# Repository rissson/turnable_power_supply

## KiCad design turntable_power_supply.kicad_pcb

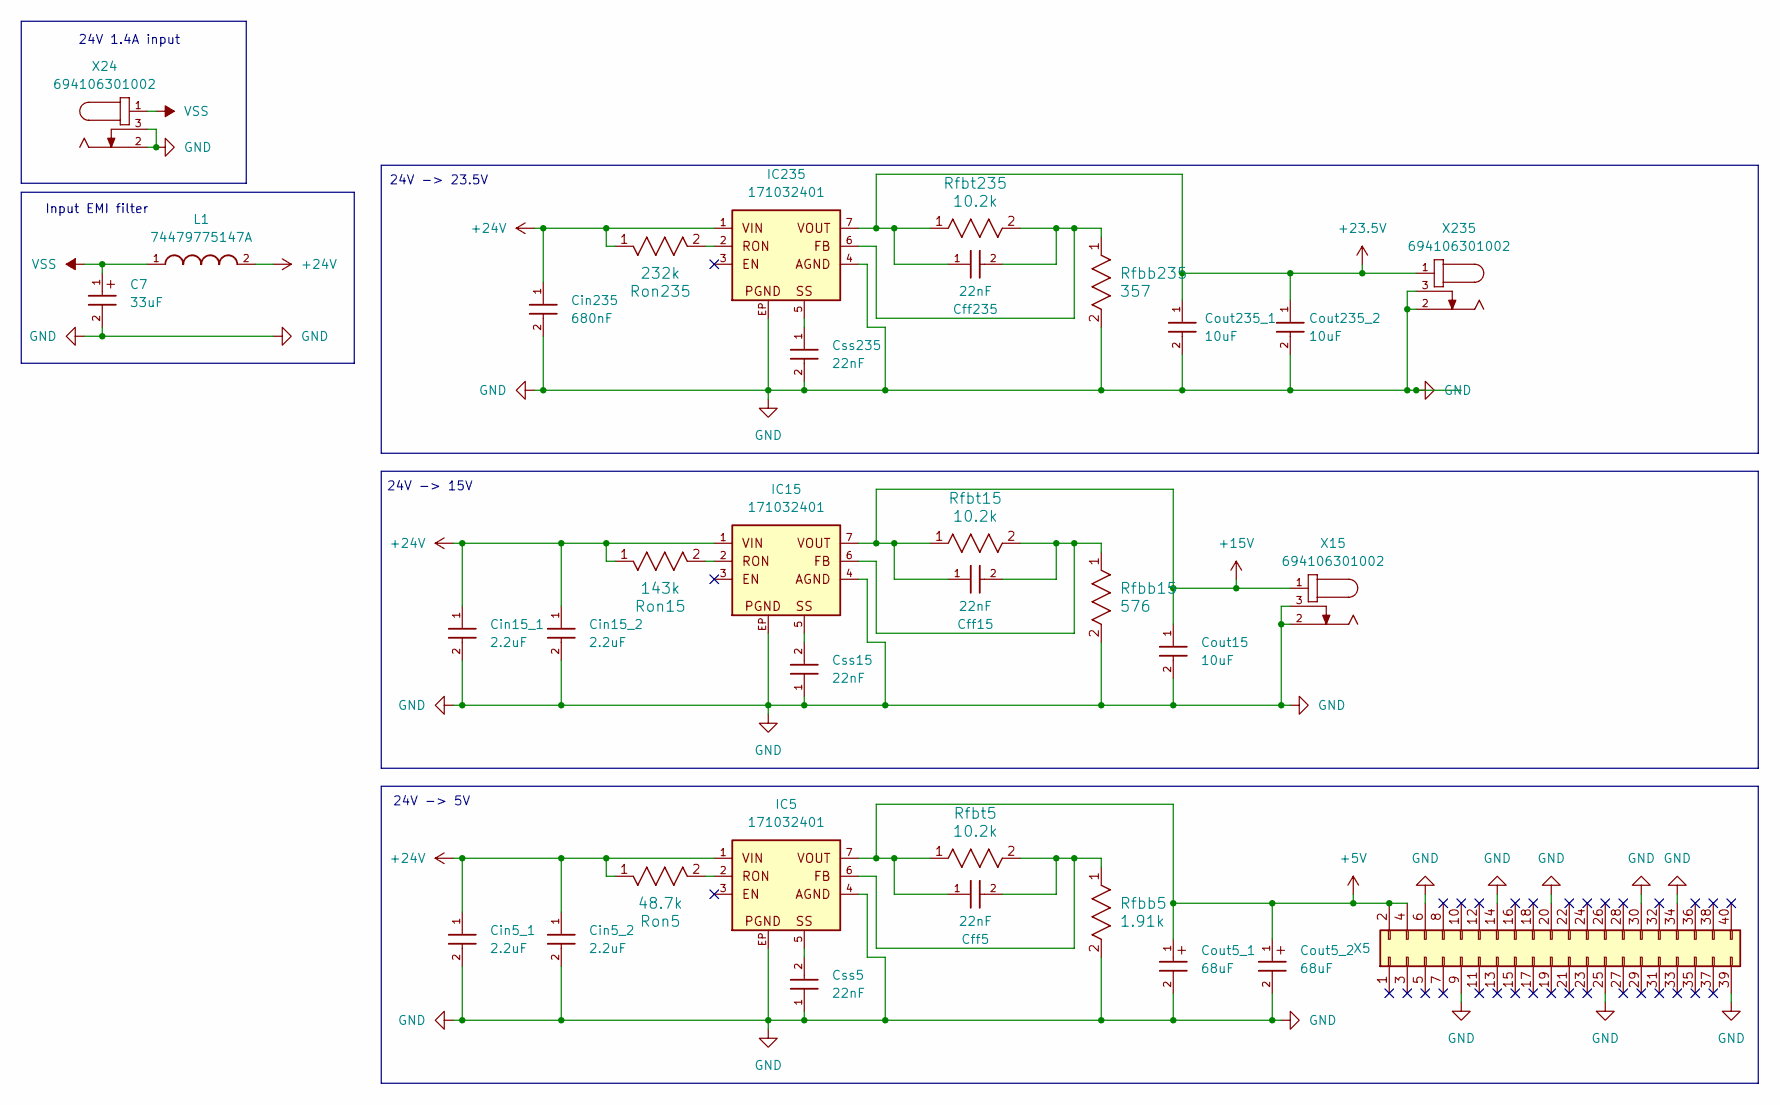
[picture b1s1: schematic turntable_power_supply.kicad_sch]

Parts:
C7: 33uF; 875115655013
Cff5, Cff15, Cff235: 22nF; 885012008009
Cin5_1, Cin5_2, Cin15_1, Cin15_2: 2.2uF; 885012210032
Cin235: 680nF; 885012210030
Cout5_1, Cout5_2: 68uF; 870235674004
Cout15: 10uF; 885012214005
Cout235_1, Cout235_2: 10uF; 885012214006
Css5, Css15, Css235: 22nF; 885012207013
IC5, IC15, IC235: 171032401; PART-NUMBER 171032401
L1: 74479775147A
Rfbb5: 1.91k; RC1206FR-071K91L
Rfbb15: 576; RC1206FR-07576RL
Rfbb235: 357; RC1206FR-07357RL
Rfbt5, Rfbt15, Rfbt235: 10.2k; RC1206FR-0710K2L
Ron5: 48.7k; RC1206FR-0748K7L
Ron15: 143k; RC1206FR-07143KL
Ron235: 232k; RC1206FR-07232KL
X5: PRT-21570; PinHeader_2x20_P2.54mm_Vertical
X15, X24, X235: 694106301002; PART-NUMBER 694106301002

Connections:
+5V: Cff5.1, Cout5_1.1, Cout5_2.1, IC5.7, Rfbt5.1, X5.2, X5.4
+15V: Cff15.1, Cout15.1, IC15.7, Rfbt15.1, X15.1
+23.5V: Cff235.1, Cout235_1.1, Cout235_2.1, IC235.7, Rfbt235.1, X235.1
+24V: Cin5_1.1, Cin5_2.1, Cin15_1.1, Cin15_2.1, Cin235.1, IC5.1, IC15.1, IC235.1, L1.2, Ron5.1, Ron15.1, Ron235.1
GND: C7.2, Cin5_1.2, Cin5_2.2, Cin15_1.2, Cin15_2.2, Cin235.2, Cout5_1.2, Cout5_2.2, Cout15.2, Cout235_1.2, Cout235_2.2, Css5.1, Css15.1, Css235.2, IC5.4, IC5.EP, IC15.4, IC15.EP, IC235.4, IC235.EP, Rfbb5.2, Rfbb15.2, Rfbb235.2, X5.6, X5.9, X5.14, X5.20, X5.25, X5.30, X5.34, X5.39, X15.2, X15.3, X24.2, X24.3, X235.2, X235.3
unnamed: Cff5.2, IC5.6, Rfbb5.1, Rfbt5.2
unnamed: Cff15.2, IC15.6, Rfbb15.1, Rfbt15.2
unnamed: Cff235.2, IC235.6, Rfbb235.1, Rfbt235.2
unnamed: Css5.2, IC5.5
unnamed: Css15.2, IC15.5
unnamed: Css235.1, IC235.5
unnamed: IC5.2, Ron5.2
unnamed: IC15.2, Ron15.2
unnamed: IC235.2, Ron235.2
VSS: C7.1, L1.1, X24.1

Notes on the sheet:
24V 1.4A input
Input EMI filter
24V -> 15V
24V -> 23.5V
24V -> 5V

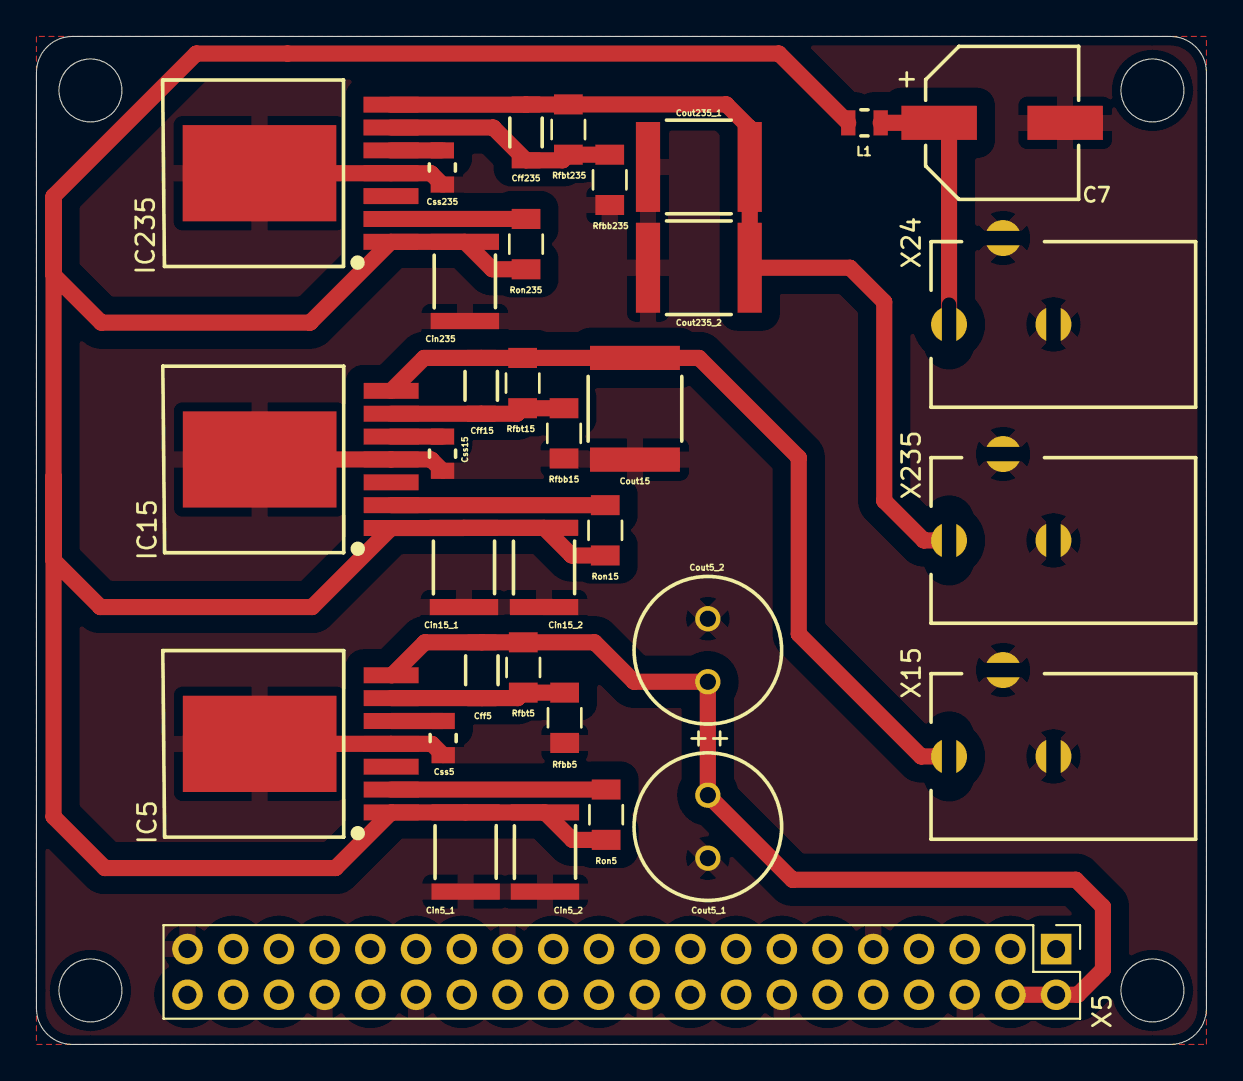
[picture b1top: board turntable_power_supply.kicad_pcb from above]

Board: 2 copper layers, 65.0 x 56.0 mm, 34 parts (0 on the bottom side), 15 nets.

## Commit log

2025-01-18 Add missing capacitors
2025-01-18 Add 3D models
2025-01-19 Add missing trace
2025-01-20 Fix Cout_15 footprint
